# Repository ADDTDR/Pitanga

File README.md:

# Pitanga Project

Prototype 0.01            |  Pitanga V1 |  Pitanga V2.1a
:-------------------------:|:-------------------------:|:-------------------------:
  |    | 

<!-- # Prototype A 
```LTP-305G```

# First version 
```ALS340A1 installed``` 

Als340A1 and ALS340A

ALS340A, ALS230A1, LTP305R, LTP305G

ALS340A1

# Version 2.1a
```LTP 305R```
 -->

## 3D

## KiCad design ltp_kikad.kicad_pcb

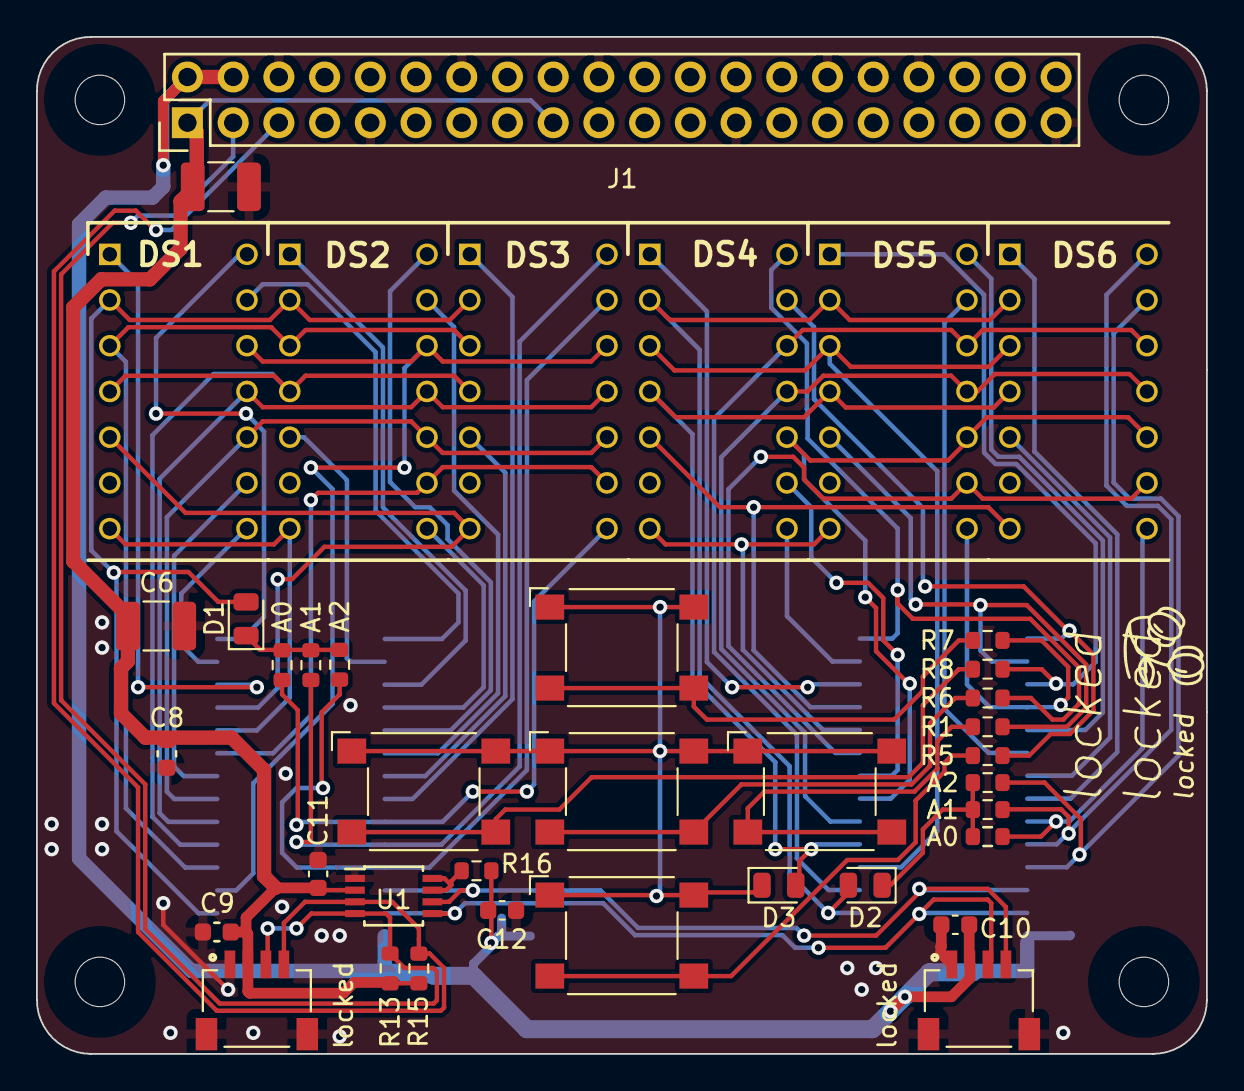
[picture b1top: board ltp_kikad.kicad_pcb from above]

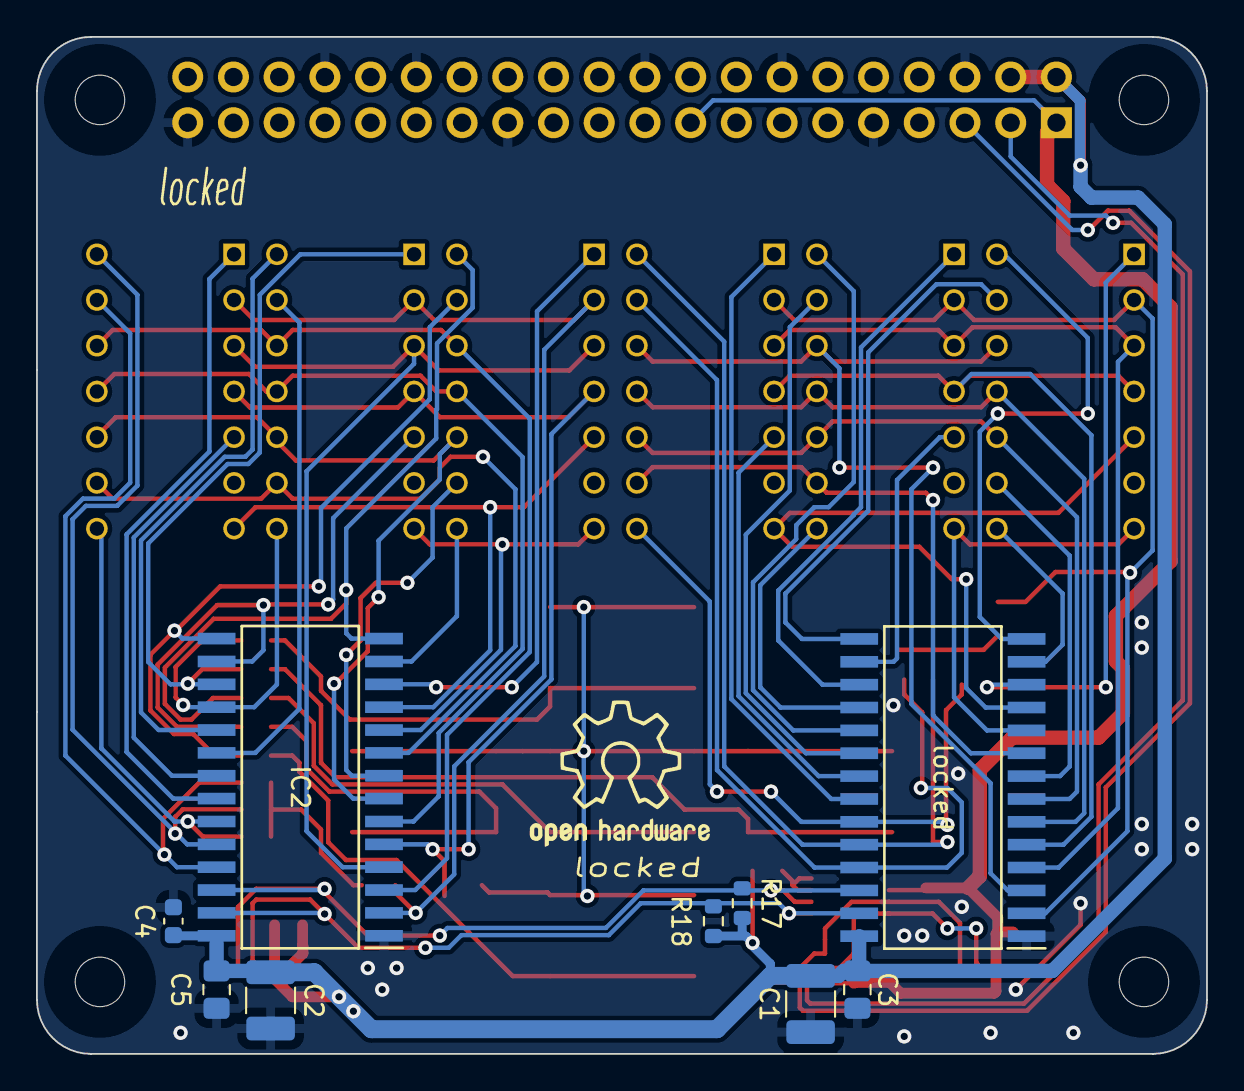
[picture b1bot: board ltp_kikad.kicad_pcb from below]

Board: 2 copper layers, 65.0 x 56.5 mm, 48 parts (9 on the bottom side), 64 nets.

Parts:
C1, C2, C6, C7: 15uF; C_1210_3225Metric_Pad1.33x2.70mm_HandSolder
C3, C5: 10uF; C_0805_2012Metric_Pad1.18x1.45mm_HandSolder
C4, C9, C10: 10uF; C_0603_1608Metric
C8, C11, C12: 0.1uF; C_0603_1608Metric
D1, D2, D3: 1N4148; D_0805_2012Metric
DS1, DS2, DS3, DS4, DS5, DS6: LTP-305G; DIPS762W50P254L1850H400Q14N
IC2: SamacSys_Parts_HT16K33-28SOP; SOIC127P1031X264-28N
J1: RPi_GPIO; Pin_Header_Straight_2x20
J2, J3: SM04B-SRSS-TB(LF)(SN); JST_SM04B-SRSS-TB(LF)(SN)
R1, R2, R3, R4, R5, R6, R7, R8, R9, R10, R11, R13: 47k; R_0603_1608Metric
R15: 10k; R_0603_1608Metric
R16: 200k; R_0603_1608Metric
R17, R18: i2c; R_0603_1608Metric
SW1, SW2, SW3, SW4, SW5: SW_Omron_B3FS; SW_SPST_Omron_B3FS-105xP
U1: PCA9306DP; TSSOP-8_3x3mm_P0.65mm
locked: SamacSys_Parts_HT16K33-28SOP; SOIC127P1031X264-28N

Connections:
2_an0: DS6.13 (ANODE_COLUMN_5), IC2.25 (ROW0/A2), R9.2
2_an1: DS6.14 (ANODE_COLUMN_4), IC2.24 (ROW1/A1), R10.2
2_an2: DS6.8 (ANODE_COLUMN_3), IC2.23 (ROW2/A0), R11.2
2_an3: DS6.1 (ANODE_COLUMN_2), IC2.22 (ROW3/K1)
2_an4: DS6.5 (ANODE_COLUMN_1), IC2.21 (ROW4/K2)
2_an5: DS5.13 (ANODE_COLUMN_5), IC2.20 (ROW5/K3)
2_an6: DS5.14 (ANODE_COLUMN_4), IC2.19 (ROW6/K4)
2_an7: DS5.8 (ANODE_COLUMN_3), IC2.18 (ROW7/K5), R7.2
2_an8: DS5.1 (ANODE_COLUMN_2), IC2.17 (ROW8/K6), R8.2
2_an9: DS5.5 (ANODE_COLUMN_1), IC2.16 (ROW9/K7), R1.2
2_an10: DS4.13 (ANODE_COLUMN_5), IC2.15 (ROW10/K8), R5.2
2_an11: DS4.14 (ANODE_COLUMN_4), IC2.14 (ROW11/K9), R6.2
2_an12: DS4.8 (ANODE_COLUMN_3), IC2.13 (ROW12/K10)
2_an13: DS4.1 (ANODE_COLUMN_2), IC2.12 (ROW13/K11)
2_an14: DS4.5 (ANODE_COLUMN_1), DS6.7 (ANODE_DECIMAL_POINT), IC2.11 (ROW14/K12)
2_an15: DS4.7 (ANODE_DECIMAL_POINT), DS5.7 (ANODE_DECIMAL_POINT), IC2.10 (ROW15/K13/INT)
2_ca0: D2.2 (A), DS4.2 (CATHODE_ROW_1), DS5.2 (CATHODE_ROW_1), DS6.2 (CATHODE_ROW_1), IC2.2 (COM0/AD)
2_ca1: DS4.12 (CAATHODE_ROW_2), DS5.12 (CAATHODE_ROW_2), DS6.12 (CAATHODE_ROW_2), IC2.3 (COM1/KS0)
2_ca2: DS4.3 (CATHODE_ROW_3), DS5.3 (CATHODE_ROW_3), DS6.3 (CATHODE_ROW_3), IC2.4 (COM2/KS1)
2_ca3: D3.2 (A), DS4.4 (CATHODE_ROW_4), DS5.4 (CATHODE_ROW_4), DS6.4 (CATHODE_ROW_4), IC2.5 (COM3/KS2)
2_ca4: DS4.11 (CATHODE__ROW_5), DS5.11 (CATHODE__ROW_5), DS6.11 (CATHODE__ROW_5), IC2.6 (COM4)
2_ca5: DS4.10 (CATHODE_ROW_6), DS5.10 (CATHODE_ROW_6), DS6.10 (CATHODE_ROW_6), IC2.7 (COM5)
2_ca6: DS4.9 (CATHODE_ROW_7), IC2.8 (COM6)
2_ca7: DS5.9 (CATHODE_ROW_7), DS6.9 (CATHODE_ROW_7), IC2.9 (COM7)
5vSCL: IC2.26 (SCL), J2.4, R17.1, U1.6 (SCL2), locked.26 (SCL)
5vSDA: IC2.27 (SDA), J2.3, R18.1, U1.5 (SDA2), locked.27 (SDA)
+3V3: C6.2, C7.2, C8.2, C9.1, C11.1, J1.1 (3.3V), J1.17 (3.3V), J3.2, R13.2, R15.2, U1.2 (VREF1)
+5V: C1.2, C2.2, C3.1, C4.1, C5.1, C10.1, C12.1, IC2.28 (VDD), J1.2 (5V), J1.4 (5V), J2.2, R16.1, R17.2, R18.2, locked.28 (VDD)
GND: C1.1, C2.1, C3.2, C4.2, C5.2, C6.1, C7.1, C8.1, C9.2, C10.2, C11.2, C12.2, IC2.1 (VSS), J1.6 (GND), J1.9 (GND), J1.14 (GND), J1.20 (GND), J1.25 (GND), J1.30 (GND), J1.34 (GND), J1.39 (GND), J2.1, J2.S1 (SHIELD), J2.S2 (SHIELD), J3.1, J3.S1 (SHIELD), J3.S2 (SHIELD), U1.1 (GND), locked.1 (VSS)
unnamed: D1.1 (K), R2.1, R3.1, R4.1
unnamed: D2.1 (K), R9.1, R10.1, R11.1
unnamed: R1.1, SW1.2
unnamed: R5.1, SW3.2
unnamed: R6.1, SW4.2
unnamed: R7.1, SW2.2
unnamed: R8.1, SW5.2
unnamed: R16.2, U1.7 (VREF2), U1.8 (EN)
SCL: J1.5 (BCM3_SCL), J3.4, R15.1, U1.3 (SCL1)
SDA: J1.3 (BCM2_SDA), J3.3, R13.1, U1.4 (SDA1)
an0: DS3.13 (ANODE_COLUMN_5), R2.2, locked.25 (ROW0/A2)
an1: DS3.14 (ANODE_COLUMN_4), R3.2, locked.24 (ROW1/A1)
an2: DS3.8 (ANODE_COLUMN_3), R4.2, locked.23 (ROW2/A0)
an3: DS3.1 (ANODE_COLUMN_2), locked.22 (ROW3/K1)
an4: DS3.5 (ANODE_COLUMN_1), locked.21 (ROW4/K2)
an5: DS2.13 (ANODE_COLUMN_5), locked.20 (ROW5/K3)
an6: DS2.14 (ANODE_COLUMN_4), locked.19 (ROW6/K4)
an7: DS2.8 (ANODE_COLUMN_3), locked.18 (ROW7/K5)
an8: DS2.1 (ANODE_COLUMN_2), locked.17 (ROW8/K6)
an9: DS2.5 (ANODE_COLUMN_1), locked.16 (ROW9/K7)
an10: DS1.13 (ANODE_COLUMN_5), locked.15 (ROW10/K8)
an11: DS1.14 (ANODE_COLUMN_4), locked.14 (ROW11/K9)
an12: DS1.8 (ANODE_COLUMN_3), locked.13 (ROW12/K10)
an13: DS1.1 (ANODE_COLUMN_2), locked.12 (ROW13/K11)
an14: DS1.5 (ANODE_COLUMN_1), DS3.7 (ANODE_DECIMAL_POINT), locked.11 (ROW14/K12)
an15: DS1.7 (ANODE_DECIMAL_POINT), DS2.7 (ANODE_DECIMAL_POINT), locked.10 (ROW15/K13/INT)
ca0: D1.2 (A), DS1.2 (CATHODE_ROW_1), DS2.2 (CATHODE_ROW_1), DS3.2 (CATHODE_ROW_1), locked.2 (COM0/AD)
ca1: DS1.12 (CAATHODE_ROW_2), DS2.12 (CAATHODE_ROW_2), DS3.12 (CAATHODE_ROW_2), locked.3 (COM1/KS0)
ca2: DS1.3 (CATHODE_ROW_3), DS2.3 (CATHODE_ROW_3), DS3.3 (CATHODE_ROW_3), locked.4 (COM2/KS1)
ca3: DS1.4 (CATHODE_ROW_4), DS2.4 (CATHODE_ROW_4), DS3.4 (CATHODE_ROW_4), locked.5 (COM3/KS2)
ca4: DS1.11 (CATHODE__ROW_5), DS2.11 (CATHODE__ROW_5), DS3.11 (CATHODE__ROW_5), locked.6 (COM4)
ca5: DS1.10 (CATHODE_ROW_6), DS2.10 (CATHODE_ROW_6), DS3.10 (CATHODE_ROW_6), locked.7 (COM5)
ca6: DS1.9 (CATHODE_ROW_7), locked.8 (COM6)
ca7: DS2.9 (CATHODE_ROW_7), DS3.9 (CATHODE_ROW_7), locked.9 (COM7)
sw_ks2: D3.1 (K), SW1.1, SW2.1, SW3.1, SW4.1, SW5.1

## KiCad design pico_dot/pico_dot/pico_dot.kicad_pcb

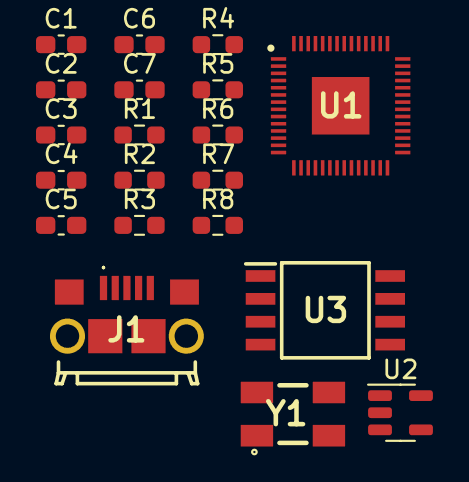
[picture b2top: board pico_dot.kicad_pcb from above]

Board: 2 copper layers, 20 parts (0 on the bottom side), 18 nets, no tracks yet.

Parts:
C1, C2, C3, C5: 1uF; C_0603_1608Metric_Pad1.08x0.95mm_HandSolder
C4, C6: 27pF; C_0603_1608Metric_Pad1.08x0.95mm_HandSolder
C7: 0.1uF; C_0603_1608Metric_Pad1.08x0.95mm_HandSolder
J1: 10118193-0001LF; 101181930001LF
R1, R2, R8: 10K; R_0603_1608Metric_Pad0.98x0.95mm_HandSolder
R3, R4: 27; R_0603_1608Metric_Pad0.98x0.95mm_HandSolder
R5: DNP; R_0603_1608Metric_Pad0.98x0.95mm_HandSolder
R6, R7: 1K; R_0603_1608Metric_Pad0.98x0.95mm_HandSolder
U1: RP2040; QFN40P700X700X90-57N-D
U2: AP2112K-3.3TRG1; SOT-23-5
U3: W25Q16JVSSIQ; SOIC127P790X216-8N
Y1: 12MHZ; ABM3B

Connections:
+3V3: C2.1, C5.1, C7.1, R1.1, R8.1, U1.1 (IOVDD), U1.10 (IOVDD), U1.22 (IOVDD), U1.33 (IOVDD), U1.42 (IOVDD), U1.43 (ADC_AVDD), U1.44 (VREG_VIN), U1.48 (USB_VDD), U1.49 (IOVDD), U2.5 (VOUT), U3.8 (VCC)
/+1.1V: C3.1, U1.23 (DVDD), U1.45 (VREG_VOUT), U1.50 (DVDD)
/QSPI_CS: R7.1, R8.2, U1.56 (QSPI_SS_N), U3.1 (~CS)
/QSPI_SCK: U1.52 (QSPI_SCLK), U3.6 (CLK)
/QSPI_SD0: U1.53 (QSPI_SD0), U3.5 (DI(IO0))
/QSPI_SD1: U1.55 (QSPI_SD1), U3.2 (DO(IO1))
/QSPI_SD2: U1.54 (QSPI_SD2), U3.3 (~WP(IO2))
/QSPI_SD3: U1.51 (QSPI_SD3), U3.7 (~HOLD/RESET(IO3))
/RUN: R1.2, U1.26 (RUN)
/USB_N: J1.2 (D-), R4.1
/USB_P: J1.3 (D+), R3.1
/VSYS: C1.1, R2.1, U2.1 (VIN)
/XIN: C4.1, R5.2, U1.20 (XIN), Y1.1
/XOUT: R5.1, R6.1, U1.21 (XOUT)
GND: C2.2, C3.2, C4.2, C6.2, C7.2, U1.19 (TESTEN), U1.57 (GND), U2.2 (GND), U3.4 (GND), Y1.2, Y1.4
unnamed: C6.1, R6.2, Y1.3
unnamed: R4.2, U1.46 (USB_DM)
unnamed: R3.2, U1.47 (USB_DP)

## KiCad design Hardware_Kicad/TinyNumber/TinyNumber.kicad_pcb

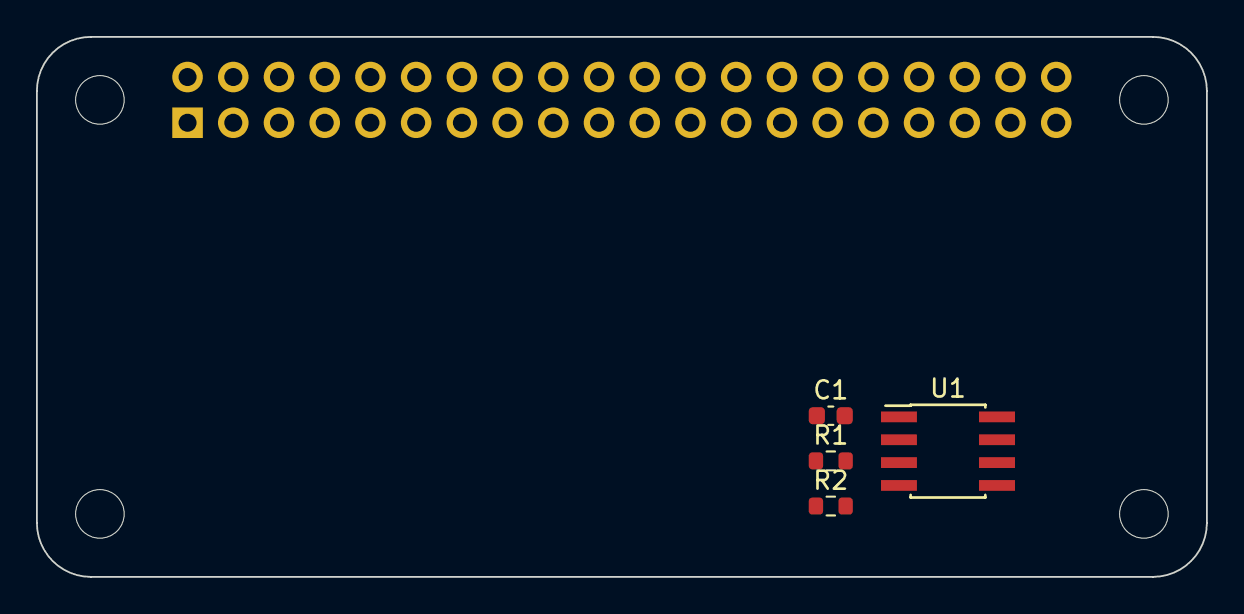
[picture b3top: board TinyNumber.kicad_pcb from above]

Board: 2 copper layers, 65.0 x 30.0 mm, 9 parts (1 on the bottom side), 5 nets, no tracks yet.

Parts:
C1: 100n; C_0603_1608Metric
J1: GPIO; PinSocket_2x20_P2.54mm_Vertical
MH1, MH2, MH3, MH4: MountingHole_2.7mm_M2.5
R1, R2: 3.9k; R_0603_1608Metric
U1: CAT24C256; PowerIntegrations_SO-8

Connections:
+3V3: C1.1, J1.1, J1.17, R1.1, R2.1, U1.8 (VCC)
+5V: J1.2, J1.4
/ID_SCL: J1.28, R2.2, U1.6 (SCL)
/ID_SDA: J1.27, R1.2, U1.5 (SDA)
GND: C1.2, J1.6, J1.9, J1.14, J1.20, J1.25, J1.30, J1.34, J1.39, U1.4 (GND)

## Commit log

2023-07-13 Add 3d device render
2023-07-18 Minimize vias transitions, optimize traces
2023-07-24 Minor improvements
2023-07-24 Add bypas cap
2023-07-25 Optimize connection routes
2023-07-25 Shorten some routes
2023-07-25 Minor fixes
2023-07-26 Add qwiic stemma i2c connector
2023-07-27 Optimize design, add bypass caps
2023-07-27 Optimize filled zones
2023-07-27 Optimize filled zones, minimize clearence, reroute some led traces
2023-07-27 Miscellaneous optimisation
2023-07-27 V 0.01
2023-07-27 Add product name, minor fixes
2023-07-27 Fix 40 pin footprint, bump version to 0.01a
2023-07-28 Changes to 0.01a
2023-07-29 Version 0.02
2023-07-29 Updates to 0.02
2023-07-29 Updates to 0.03
2023-07-29 Minor Updates to 0.03
2023-07-29 Add artwork and logo
2023-07-29 Add hq render, customize colors
2023-07-30 V 0.04a 0Add CAN tranciver, set 3d models for components
2023-07-31 Add PCA9306 i2c transciever
2023-07-31 Add renders
2023-07-31 Update placement, Gerade device 3d model
2023-08-01 Version 0.05
2023-08-01 Add testpoints
2023-08-02 Minimize distances between displays
2023-08-02 Fix routes
2023-08-03 Version 0.06
2023-08-03 Updates vias
2023-08-05 Add rp2040 mcu, remove mcp2515
2023-08-06 Use 402 footprint for rp2040 mcu part
2023-08-07 Update design
2023-08-07 Update update drc, move spi flash
2023-08-07 Update design place rgb led
2023-08-08 Add user buttons
2023-08-08 Reroute i2c, connect user buttons
2023-08-10 Add mcp 2517 can transceiver
2023-08-11 move to 4 layers
2023-08-11 Update routes
2023-08-11 Add CAN TVS protection
2023-08-11 Add CAN TVS routes
2023-08-12 Add CAN stby
2023-08-13 Fix can stby jumper
2023-08-14 Move power traces, to iner layer, fix some drc violations
2023-08-14 Updates 2
2023-08-14 Updates move some rotes from front layer
2023-08-17 Verssion 0.11
2023-08-17 Verssion updates to 0.11
2023-08-17 Updates, more estetic routes, change silkscreen font
2023-08-18 Updates silkscreen
2023-08-29 Update crystal footprint, move i2c lines to iner layer
2023-09-14 Fix connection on an6 an5 ds2
2023-09-29 Add pdf schematic
2023-09-30 Simplify design
2023-09-30 Fix connections
2023-09-30 Add 6mm omron tactile switches
2023-09-30 Route switches connections
2023-10-01 Pitanga Hat V1
2023-10-01 Add address resistors
2023-10-01 Connect decimal points ds3 ds5, add cap
2023-10-01 Add gerber files
2023-10-02 Move j2 silkscreen
2023-10-04 Add dot pretty folder to store componets
2023-10-05 Separate libraries
2023-10-05 3D models path for pcd viewer
2023-10-05 Update silk screen values
2023-10-05 Set ltp 305 3d model path
2023-10-05 Update polygons
2023-10-05 Update silkscreen
2023-10-05 Reroute front traces
2023-10-05 Optimise few routes
2023-10-05 Optimise routes, add caps
2023-10-10 Add proto area
2023-10-14 Add inductor
2023-10-14 Add dc-dc 3.3v to 5v
2023-10-14 Add i2c transciever, Pitanga V2
2023-10-15 Add Pitanga V2 gerbers
2023-10-17 Add Pitanga V2 renders
2023-10-18 Minor updates
2023-10-19 Fix decimal point connection on ds4, add info to title block
2023-10-19 Pitanga 2.1
2023-10-20 Add gitignore file, stop tracking zip files
2023-10-20 Add pdf schematic for v2.1
2023-10-20 Change buttons
2023-10-20 Change tactile shwitches
2023-10-20 Add title block
2023-10-20 Finilize small buttons
2023-10-21 Mutimplex cat6 and cat7 conect decimal point on second diplay module
2023-10-21 Add second decimal connection to first led driver
2023-10-21 Remove isolated gnd areas
2023-10-21 Update library
2023-10-21 Update ltp305 footprint
2023-10-21 Realease v2.1 with 6mm buttons
2023-11-04 Piatnag_5_bt
2023-11-05 Move from 4 layer to 2, complete roting, separate 5v for led driver and 3v i2c power
2023-11-06 Veryfy, connection, label. i2c connectors
2023-11-06 Add development and testing photo
2023-11-06 Add hd renders
2024-02-04 Folders refactor
2024-02-08 Add Pitaga 3D board export
2024-02-26 Add blender project
2025-02-12 Add license
